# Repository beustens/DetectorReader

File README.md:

# Detector Reader
Short range, low cost UHF RFID reader based on RF detector

## Features
- 0.5m...2m read range depending on antenna and tag (8dBi patch antenna recommended)
- Monostatic or bistatic configuration
- ~15$ of production cost
- Compact size of 46x25mm
- Powersupply via 3...5V or USB
- EPCs are reported via UART or USB (serial) interface (115200 baud)

## Flashing
The firmware is written in AVR-C for the ATtiny814 using the platformIO IDE (extension for Visual STudio Code).

To transfer the firmware to the microcontroller, install [pymcuprog](https://pypi.org/project/pymcuprog/) and build yourself a UPDI programmer from a simple USB-UART converter and a 1kOhm resistor by connecting the resistor between Rx und Tx and connecting Rx to UPDI (Reset pin):
```
                        Vcc                     Vcc
                        +-+                     +-+
                         |                       |
 +---------------------+ |                       | +--------------------+
 | Serial port         +-+                       +-+  AVR device        |
 |                     |     +----------+          |                    |
 |                  TX +-----+   1k     +-----+    |                    |
 |                     |     +----------+     |    |                    |
 |                     |                      |    |                    |
 |                  RX +----------------------+----+ UPDI               |
 |                     |                           |                    |
 |                     +--+                     +--+                    |
 +---------------------+  |                     |  +--------------------+
                         +-+                   +-+
                         GND                   GND
```

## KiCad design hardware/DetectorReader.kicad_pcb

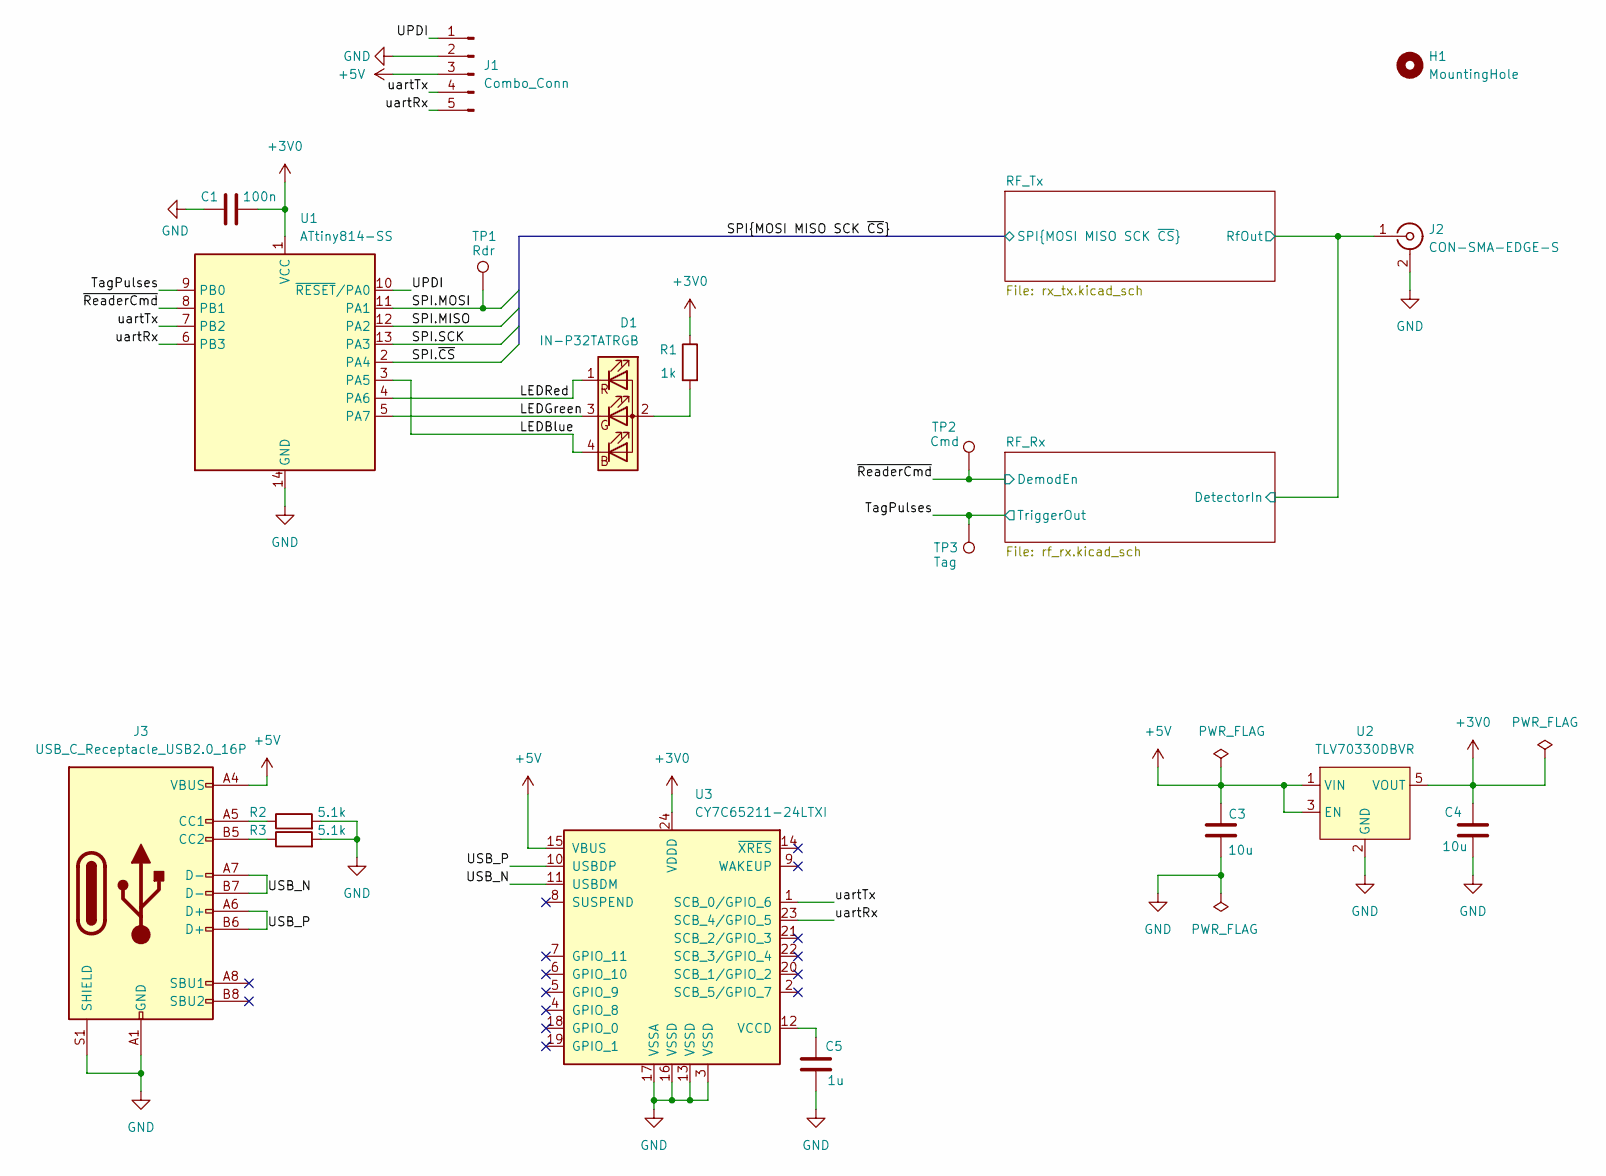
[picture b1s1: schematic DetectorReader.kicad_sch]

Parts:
C1: 100n; C_0603_1608Metric
C3, C4: 10u; C_0603_1608Metric
C5: 1u; C_0603_1608Metric
D1: IN-P32TATRGB; LED_SMD_IN-P32TATRGB
H1: MountingHole; MountingHole_3.2mm_M3_DIN965
J1: Combo_Conn; PinHeader_1x05_P2.54mm_Vertical
J2: CON-SMA-EDGE-S; SMA_Samtec_SMA-J-P-H-ST-EM1_EdgeMount
J3: USB_C_Receptacle_USB2.0_16P; USB_C_Receptacle_GCT_USB4105-xx-A_16P_TopMnt_Horizontal
R1: 1k; R_0603_1608Metric
R2, R3: 5.1k; R_0603_1608Metric
TP1: Rdr; Single_Pin
TP2: Cmd; Single_Pin
TP3: Tag; Single_Pin
U1: ATtiny814-SS; SOIC-14_3.9x8.7mm_P1.27mm
U2: TLV70330DBVR; SOT-23-5
U3: CY7C65211-24LTXI; QFN-24-1EP_4x4mm_P0.5mm_EP2.6x2.6mm

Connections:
+3V0: C1.2, C4.2, R1.1, U1.1 (VCC), U2.5 (VOUT), U3.24 (VDDD); also elsewhere on the board
+5V: C3.2, J1.3, J3.A4 (VBUS), J3.A9 (VBUS), J3.B4 (VBUS), J3.B9 (VBUS), U2.1 (VIN), U2.3 (EN), U3.15 (VBUS)
/LEDBlue: D1.4 (BK), U1.3 (PA5)
/LEDGreen: D1.3 (GK), U1.5 (PA7)
/LEDRed: D1.1 (RK), U1.4 (PA6)
/RF_Rx/DetectorIn: J2.1 (In); also elsewhere on the board
/SPI.MISO: U1.12 (PA2); also elsewhere on the board
/SPI.MOSI: TP1.1 (1_1), U1.11 (PA1); also elsewhere on the board
/SPI.SCK: U1.13 (PA3); also elsewhere on the board
/SPI.~CS: U1.2 (PA4); also elsewhere on the board
/TagPulses: TP3.1 (1_1), U1.9 (PB0); also elsewhere on the board
/UPDI: J1.1, U1.10 (~RESET/PA0)
/USB_N: J3.A7 (D-), J3.B7 (D-), U3.11 (USBDM)
/USB_P: J3.A6 (D+), J3.B6 (D+), U3.10 (USBDP)
/uartRx: J1.5, U1.6 (PB3), U3.23 (SCB_4/GPIO_5)
/uartTx: J1.4, U1.7 (PB2), U3.1 (SCB_0/GPIO_6)
/~ReaderCmd: TP2.1 (1_1), U1.8 (PB1); also elsewhere on the board
GND: C1.1, C3.1, C4.1, C5.1, J1.2, J2.2 (Ext), J3.A1 (GND), J3.A12 (GND), J3.B1 (GND), J3.B12 (GND), J3.S1 (SHIELD), R2.2, R3.2, U1.14 (GND), U2.2 (GND), U3.3 (VSSD), U3.13 (VSSD), U3.16 (VSSD), U3.17 (VSSA); also elsewhere on the board
unnamed: D1.2 (A), R1.2
unnamed: J3.A5 (CC1), R2.1
unnamed: J3.B5 (CC2), R3.1
unnamed: C5.2, U3.12 (VCCD)

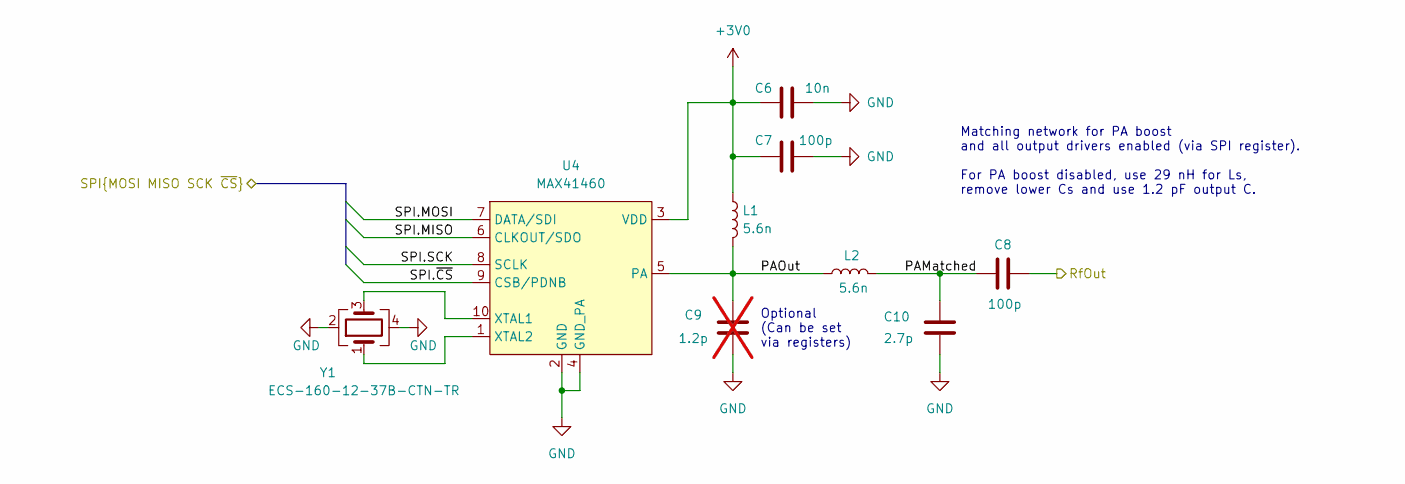
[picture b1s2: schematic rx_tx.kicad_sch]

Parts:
C6: 10n; C_0603_1608Metric
C7, C8: 100p; C_0603_1608Metric
C9: 1.2p; C_0603_1608Metric; not fitted
C10: 2.7p; C_0603_1608Metric
L1, L2: 5.6n; L_0603_1608Metric
U4: MAX41460; VSSOP-10_3x3mm_P0.5mm
Y1: ECS-160-12-37B-CTN-TR; Crystal_SMD_2016-4Pin_2.0x1.6mm

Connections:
+3V0: C6.1, C7.2, L1.1, U4.3 (VDD); also elsewhere on the board
/RF_Rx/DetectorIn: C8.1; also elsewhere on the board
/RF_Tx/PAMatched: C8.2, C10.1, L2.2
/RF_Tx/PAOut: C9.1, L1.2, L2.1, U4.5 (PA)
/SPI.MISO: U4.6 (CLKOUT/SDO); also elsewhere on the board
/SPI.MOSI: U4.7 (DATA/SDI); also elsewhere on the board
/SPI.SCK: U4.8 (SCLK); also elsewhere on the board
/SPI.~CS: U4.9 (CSB/PDNB); also elsewhere on the board
GND: C6.2, C7.1, C9.2, C10.2, U4.2 (GND), U4.4 (GND_PA), Y1.2, Y1.4; also elsewhere on the board
unnamed: U4.10 (XTAL1), Y1.3
unnamed: U4.1 (XTAL2), Y1.1

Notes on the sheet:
Optional (Can be set via registers)
Matching network for PA boost and all output drivers enabled (via SPI register). For PA boost disabled, use 29 nH for Ls, remove lower Cs and use 1.2 pF output C.

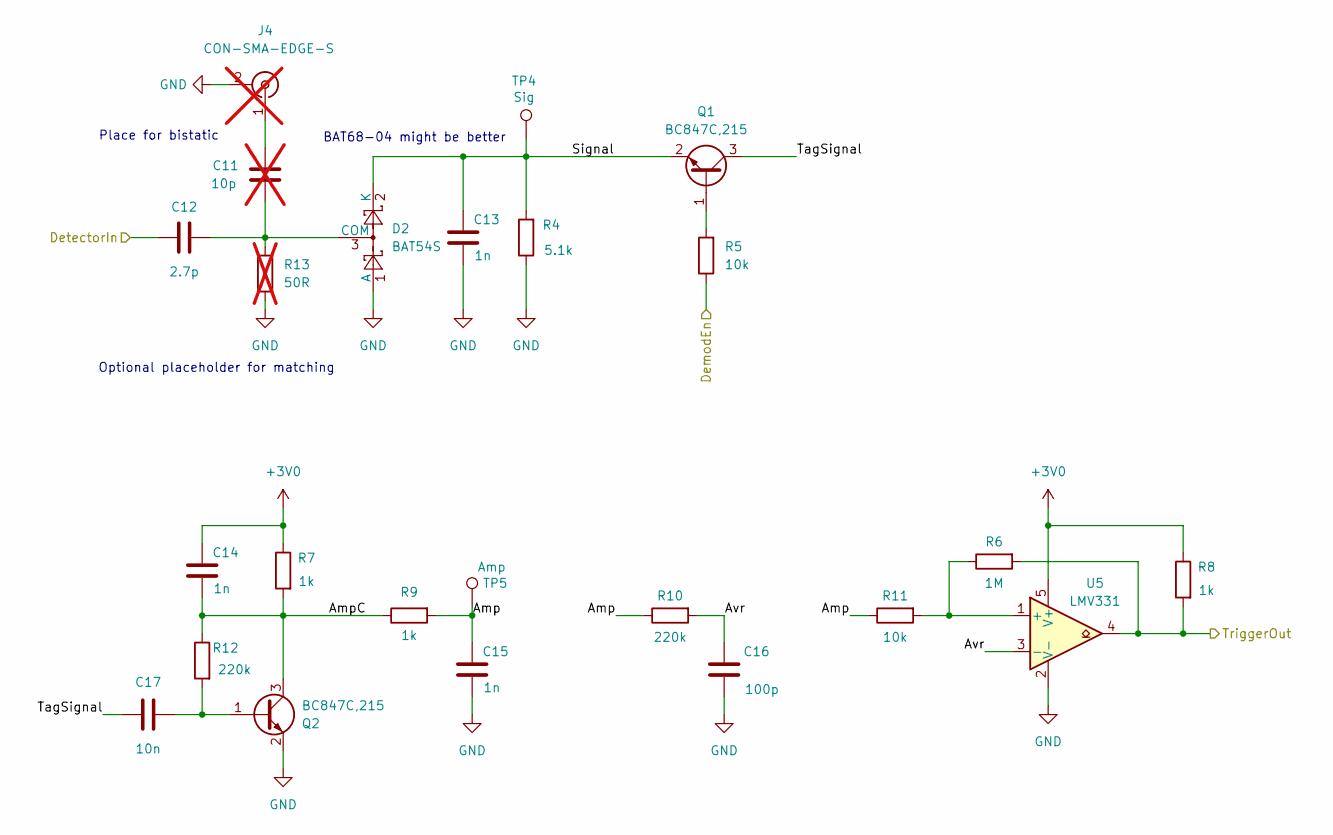
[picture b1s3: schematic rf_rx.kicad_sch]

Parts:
C11: 10p; C_0603_1608Metric; not fitted
C12: 2.7p; C_0603_1608Metric
C13, C14, C15: 1n; C_0603_1608Metric
C16: 100p; C_0603_1608Metric
C17: 10n; C_0603_1608Metric
D2: BAT54S; SOT-23
J4: CON-SMA-EDGE-S; SMA_Samtec_SMA-J-P-H-ST-EM1_EdgeMount; not fitted
Q1, Q2: BC847C,215; SOT-23
R4: 5.1k; R_0603_1608Metric
R5, R11: 10k; R_0603_1608Metric
R6: 1M; R_0603_1608Metric
R7, R8, R9: 1k; R_0603_1608Metric
R10, R12: 220k; R_0603_1608Metric
R13: 50R; R_0603_1608Metric; not fitted
TP4: Sig; Single_Pin
TP5: Amp; Single_Pin
U5: LMV331; SOT-353_SC-70-5

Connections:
+3V0: C14.1, R7.1, R8.1, U5.5 (V+); also elsewhere on the board
/RF_Rx/Amp: C15.1, R9.2, R10.1, R11.1, TP5.1 (1_1)
/RF_Rx/AmpC: C14.2, Q2.3 (C), R7.2, R9.1, R12.1
/RF_Rx/Avr: C16.1, R10.2, U5.3 (-)
/RF_Rx/DetectorIn: C12.2; also elsewhere on the board
/RF_Rx/Signal: C13.1, D2.2 (K), Q1.2 (E), R4.2, TP4.1 (1_1)
/RF_Rx/TagSignal: C17.1, Q1.3 (C)
/TagPulses: R6.2, R8.2, U5.4; also elsewhere on the board
/~ReaderCmd: R5.1; also elsewhere on the board
GND: C13.2, C15.2, C16.2, D2.1 (A), J4.2 (Ext), Q2.2 (E), R4.1, R13.2, U5.2 (V-); also elsewhere on the board
unnamed: C11.2, C12.1, D2.3 (COM), R13.1
unnamed: C11.1, J4.1 (In)
unnamed: Q1.1 (B), R5.2
unnamed: C17.2, Q2.1 (B), R12.2
unnamed: R6.1, R11.2, U5.1 (+)

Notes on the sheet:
Optional placeholder for matching
Place for bistatic
BAT68-04 might be better

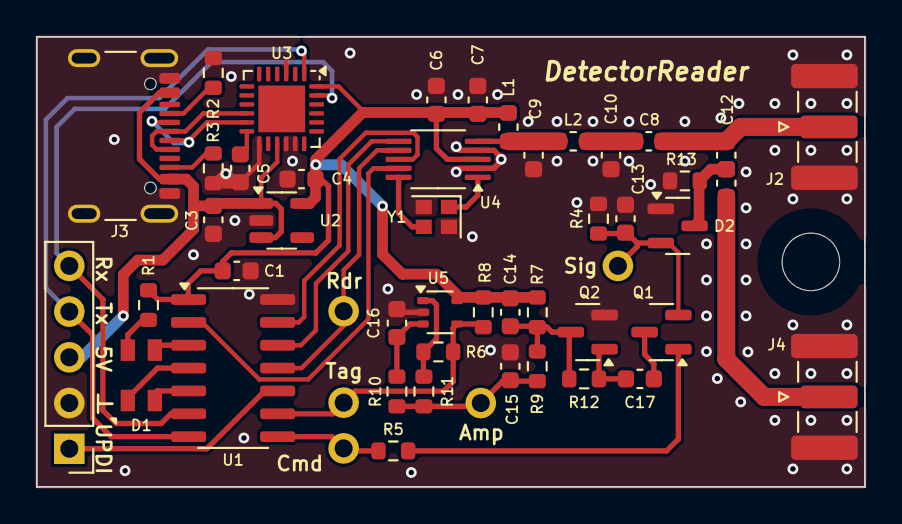
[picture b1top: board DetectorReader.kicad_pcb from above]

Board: 2 copper layers, 46.0 x 25.0 mm, 51 parts (0 on the bottom side), 36 nets.

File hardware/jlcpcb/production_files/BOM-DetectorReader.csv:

Comment,Designator,Footprint,LCSC,Quantity
MAX41460,U4,VSSOP-10_3x3mm_P0.5mm,,1
2.7p,C10,C_0603_1608Metric,,1
2.7p,C12,C_0603_1608Metric,,1
"BC847C,215",Q2,SOT-23,,1
CY7C65211-24LTXI,U3,QFN-24-1EP_4x4mm_P0.5mm_EP2.6x2.6mm,,1
10u,C4,C_0603_1608Metric,,1
IN-P32TATRGB,D1,LED_SMD_IN-P32TATRGB,,1
Combo_Conn,J1,PinHeader_1x05_P2.54mm_Vertical,,1
5.1k,R4,R_0603_1608Metric,,1
220k,R10,R_0603_1608Metric,,1
100n,C1,C_0603_1608Metric,,1
USB_C_Receptacle_USB2.0_16P,J3,USB_C_Receptacle_GCT_USB4105-xx-A_16P_TopMnt_Horizontal,,1
220k,R12,R_0603_1608Metric,,1
5.1k,R3,R_0603_1608Metric,,1
TLV70330DBVR,U2,SOT-23-5,,1
10k,R5,R_0603_1608Metric,,1
LMV331,U5,SOT-353_SC-70-5,,1
1k,R7,R_0603_1608Metric,,1
1u,C5,C_0603_1608Metric,,1
ATtiny814-SS,U1,SOIC-14_3.9x8.7mm_P1.27mm,,1
1k,R9,R_0603_1608Metric,,1
100p,C7,C_0603_1608Metric,,1
CON-SMA-EDGE-S,J2,SMA_Samtec_SMA-J-P-H-ST-EM1_EdgeMount,,1
"BC847C,215",Q1,SOT-23,,1
1k,R8,R_0603_1608Metric,,1
1M,R6,R_0603_1608Metric,,1
ECS-160-12-37B-CTN-TR,Y1,Crystal_SMD_2016-4Pin_2.0x1.6mm,,1
10k,R11,R_0603_1608Metric,,1
5.1k,R2,R_0603_1608Metric,,1
10n,C6,C_0603_1608Metric,,1
1n,C13,C_0603_1608Metric,,1
1k,R1,R_0603_1608Metric,,1
100p,C8,C_0603_1608Metric,,1
10n,C17,C_0603_1608Metric,,1
5.6n,L1,L_0603_1608Metric,,1
10u,C3,C_0603_1608Metric,,1
1n,C15,C_0603_1608Metric,,1
100p,C16,C_0603_1608Metric,,1
5.6n,L2,L_0603_1608Metric,,1
1n,C14,C_0603_1608Metric,,1
BAT54S,D2,SOT-23,,1

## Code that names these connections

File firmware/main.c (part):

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#include <avr/interrupt.h>	// for sei(), cli() and ISR()
#include <util/delay.h> // for waiting

// Command pulses progress: PA4
// Command pulses output: PA7
// Tag pulses input: PA6
// Tag preamble detected indicator output: PB2
// Tag EPC detected indicator output: PB3
// USART (alternative pin) RX: PA2
// USART (alternative pin) TX: PA1

// definitions
// general
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}

void configGPIO() {
	PORTA.DIRSET = PIN4_bm | PIN7_bm; // PA4 and PA7 as output
	PORTA.DIRCLR = PIN6_bm; // PA6 as input
	PORTA.PIN4CTRL |= PORT_INVEN_bm; // invert cmd progress output to simplify circuit
	PORTB.DIRSET = PIN3_bm | PIN2_bm; // PB2 and PB3 as output
}

void configClock() {
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	USART0.CTRLA |= USART_RXCIF_bm; // enable interrupt on receive complete
	// use alternative UART pins
	PORTMUX_CTRLB |= PORTMUX_USART0_bm; // enable alternative UART pins
	PORTA.DIRCLR = PIN2_bm; // PA2 as input (RX)
	PORTA.DIRSET = PIN1_bm; // PA1 as output (TX)
}

void sendChar(const char c) {
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void configTCB() {
	// config event
	EVSYS.ASYNCUSER0 = EVSYS_ASYNCUSER0_ASYNCCH0_gc;
	EVSYS.ASYNCCH0 = EVSYS_ASYNCCH0_PORTA_PIN6_gc; // PA6 as event trigger
	// config pulse with capture
	TCB0.CTRLB = TCB_CNTMODE_PW_gc; // set timer to pulse width measurement mode
	TCB0.CTRLA = TCB_CLKSEL_CLKDIV2_gc; // prescale timer clock by 2
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
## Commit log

2022-08-01 splitted quad opamp into dual opamp and comparator for better digitalization and smaller board
2022-08-02 added PA and changed directional coupler
2022-08-18 fixed unreliable reader query transmit
2022-08-19 Simulation with rail-to-rail opamp
2022-08-21 cleaned up simulation files
2022-08-21 simulation with one transistor and comparator works
2022-08-21 added simulation variant with dual opamp
2022-08-22 made makefile hopefully cross-platform
2022-08-23 used other part values to reduce diversity
2022-08-23 removed unused simulations
2022-08-23 increased tolerance to substantially increase read range
2022-08-23 changed resistor values in simulation to reduce diversity
2022-08-23 optimized resistor value according to real world test
2022-08-24 Updated schematic, PCB and fabrication files
2022-09-07 changed R10 to 12k to increase tag pulse detection trigger threshold
2023-03-23 added documentation
2023-07-29 updated docu and Makefile for flashing firmware using pymcuprog
2025-12-15 Rev 2. Using USB-C, configurable Tx, op-amp based LF amplifier, tri-color indicator. Using platformIO for firmware, splitted code into separate files.
2025-12-16 updated production files
2025-12-16 updated docs
2026-01-05 fixed tag pulse tracking
2026-01-09 fixed frequency pll calculation
2026-02-18 Rev 3. Back to transistor-based design since op-amp approach did not work well. Using UART bridge from other brand as FTDI was sold out.
2026-02-19 Rev 4. Removed coupler and detector IC. Using simple diode as detector.
2026-02-24 Fixed UART bridge power supply. Made board 1 mm shorter.
2026-02-24 updated documentation
2026-02-25 C12 is now 2.7pF to solve issue with too high detector voltage and reduce BOM
2026-05-23 Fixed connector pinout according to silkscreen
2026-06-25 Implemented QueryRep in firmware to read more than one tag in field
